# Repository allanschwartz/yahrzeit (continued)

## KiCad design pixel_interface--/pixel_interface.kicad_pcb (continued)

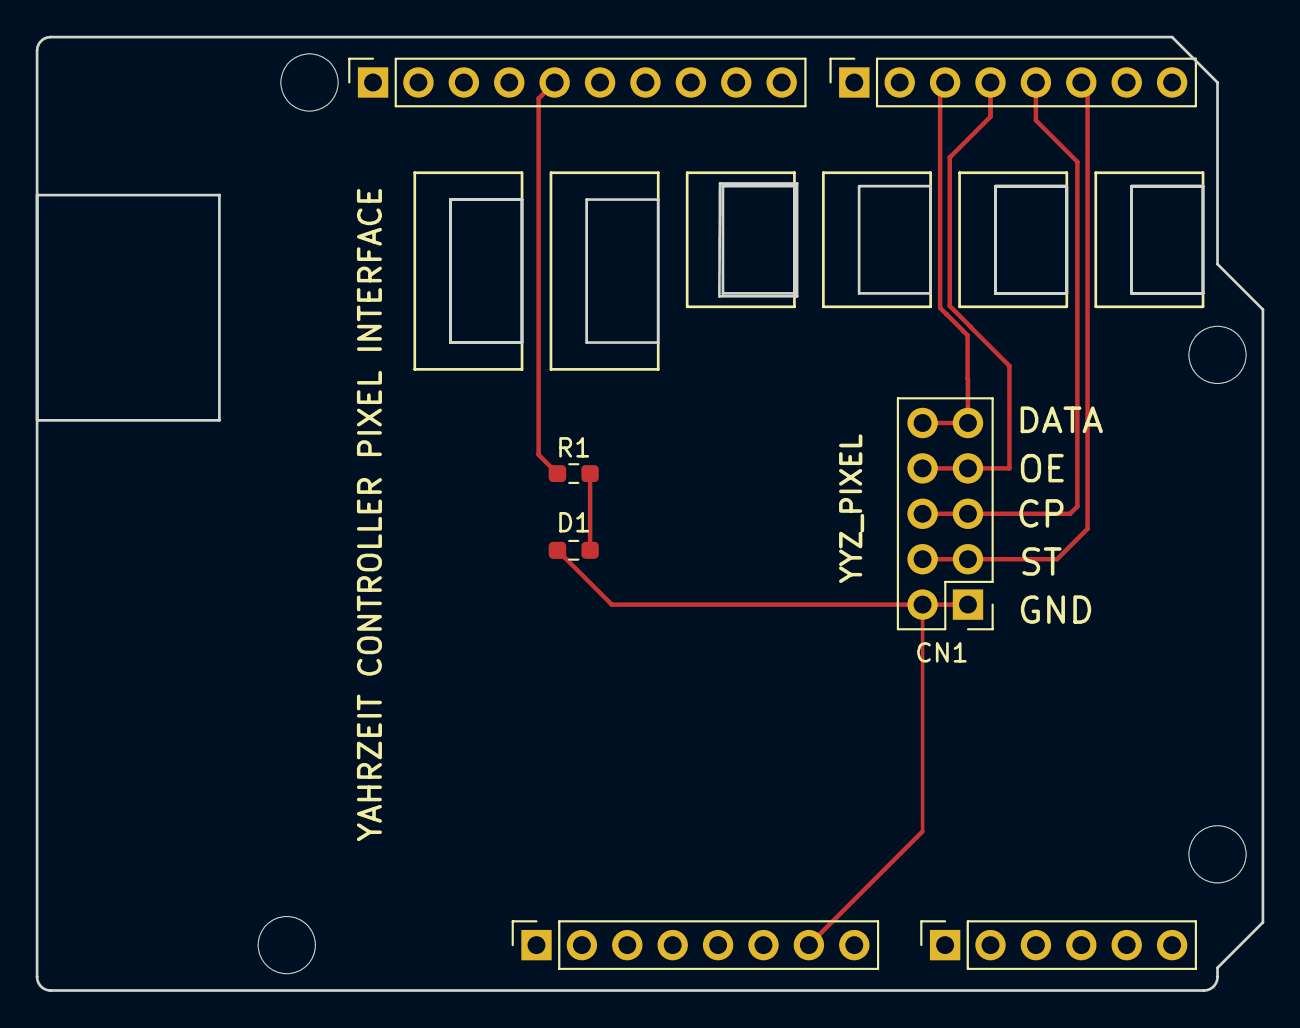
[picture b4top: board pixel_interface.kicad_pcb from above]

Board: 2 copper layers, 68.6 x 53.3 mm, 11 parts (0 on the bottom side), 9 nets.

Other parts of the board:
MH1, MH2, MH3, MH4: MountingHole_3.2mm

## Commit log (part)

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2015-07-16 Yahrzeit Wall Server
    The Congregation Beth Shalom Yahrzeit wall system, consisting of server
    code, and embedded controller code.
2015-07-27 big change july
2015-07-27 changes with Zach watching
2015-09-18 misc changes
2015-09-18 fix for Elul/Tishri
    fix for yahrzeits in Elul when this is Tishri
2017-05-02 found files
2026-04-30 Refactor: introduce YyzPixel, LedWall, and CmdProc classes; fix layering; add panic handler; working console command processor; all self-tests passing
2026-05-22 Archive current yahrzeit hardware and controller work
2026-05-22 Move one-time date conversion utility to attic
2026-05-22 Separate live yahrzeit data from historical CSV files
2026-05-22 Add cleanup notes for legacy yahrzeit PHP appliance
2026-05-22 Move obsolete transport and scratch notes to attic
2026-05-23 Unify yahrzeit command wrapper and validate controller transport
2026-05-23 Modernize yahrzeitd for PHP 8 and generate command stream
2026-05-24 Clean up yahrzeit command generation and PHP runtime support
2026-05-24 Remove obsolete RCS archive from yahrzeit site
2026-05-24 nightly checkin
2026-05-24 Simplify panel browser and add manual lighting controls
2026-05-24 Hide controller timing output behind diagnostic command
2026-05-24 Make names screen a read-only searchable browser
2026-05-24 Clean up core Yahrzeit GUI screens
2026-05-25 Add Yahrzeit reports and reorganize site support files
2026-05-25 Wire reports screen to Yahrzeit backend
2026-05-26 Clean up Yahrzeit daemon and add scheduler
2026-05-26 Document Yahrzeit include modules
2026-05-27 huge amount of documentation changes, including help files for every screen
2026-05-27 Document embedded controller architecture
2026-05-28 add styled help pages and user guide
2026-05-28 - scheduler moved to phase-based cron model - help/user-guide language updated for cron phases - Minhag help clarified: web app suggests crontab, does not install it - help pages/footer rendering cle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
2026-05-28 final version of the pixel_interface board
2026-05-29 Refactor of several php files, creating include date_support.in.php Also refactored include/paniels.inc making that clearer
2026-06-01 Refactor Yahrzeit screen entry points
2026-06-03 fixed issues in embedded .. debugged row/col in setPixel
2026-06-03 checked in the yahrzeit_pixel9 and yahrzeit_pixel12 boards into GIT
2026-06-03 xyzzy
2026-06-04 Add timeout diagnostics to controller transmit
2026-06-20 improving first screen
2026-06-20 Add safe single-record memorial editing
2026-06-20 improved the PHP code for better readability and maintainability, added new images for LED indicators, and included a new policy file for yahrzeit settings. Also updated the documentation and TODO no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
2026-06-20 adjusted comments and fuction names to use erev_shabbat instead of friday for shabbat lighting. This is a more accurate description of the time period that is being used for the yahrzeit lighting.
2026-06-20 add count of yahrzeits in the current week, and use that to decide whether to run the
2026-06-20 committing loose ends
2026-06-21 major cleanup: add project README for GitHub landing page move scheduler/install notes into docs add appliance installer script remove obsolete attic/archive artifacts and deadwood rename add-to-priv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
2026-06-21 moving everything to be more compact directories
2026-06-21 fixed geometry problems, separate out the display buffer layout, and add a README.md for the embedded code.
2026-06-24 implemented the STATUS LED breathing effect on the Yahrzeit Controller Pixel Interface board, connected to pin D3 of the Arduino Uno R4 Minima. The LED now smoothly transitions in brightness over a p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
2026-06-29 Align firmware naming with Arduino style. new "breathingLed()" function to support breathing LED effect.
